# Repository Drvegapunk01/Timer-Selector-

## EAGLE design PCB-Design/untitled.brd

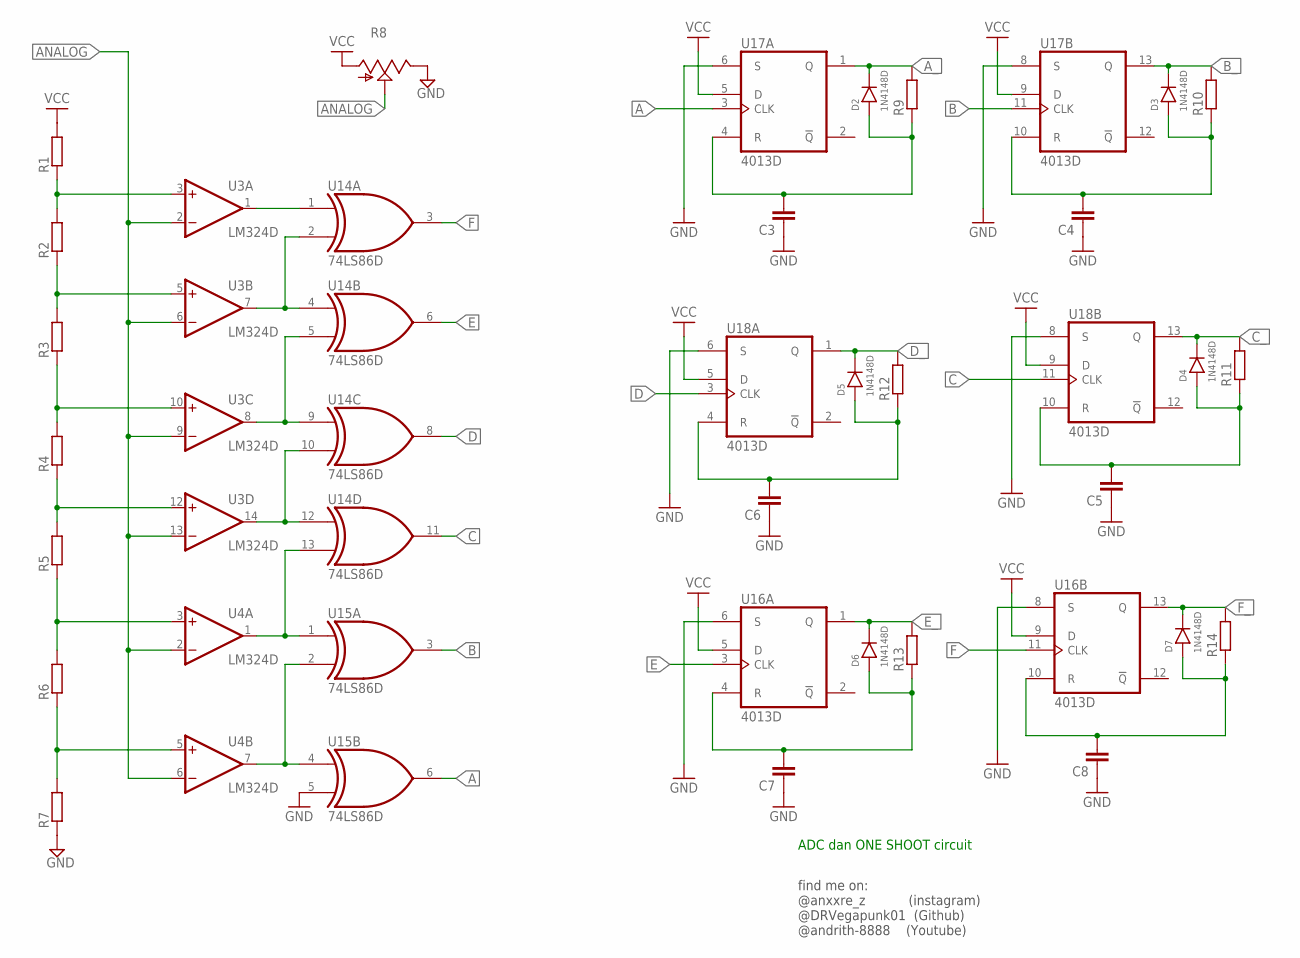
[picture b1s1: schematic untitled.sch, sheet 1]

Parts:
C3, C4, C5, C6, C7, C8: CAP-NON0805; SMD0805
D2, D3, D4, D5, D6, D7: 1N4148D; SOD80C
R1, R2, R3, R4, R5, R6, R7, R9, R10, R11, R12, R13, R14: RES0805; SMD0805
R8: TRIM_US-CT6; CT6
U3, U4: LM324D; SO14
U14, U15: 74LS86D; SO14
U16, U17, U18: 4013D; SO14

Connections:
A: U15.6 (O), U17.3 (CLK); also elsewhere on the board
ANALOG: R8.S, U3.2 (-IN), U3.6 (-IN), U3.9 (-IN), U3.13 (-IN), U4.2 (-IN), U4.6 (-IN); also elsewhere on the board
A_: D2.C (2), R9.2, U17.1 (Q); also elsewhere on the board
B: U15.3 (O), U17.11 (CLK); also elsewhere on the board
B_: D3.C (2), R10.2, U17.13 (Q); also elsewhere on the board
C: U14.11 (O), U18.11 (CLK); also elsewhere on the board
C_: D4.C (2), R11.2, U18.13 (Q); also elsewhere on the board
D: U14.8 (O), U18.3 (CLK); also elsewhere on the board
D_: D5.C (2), R12.2, U18.1 (Q); also elsewhere on the board
E: U14.6 (O), U16.3 (CLK); also elsewhere on the board
E_: D6.C (2), R13.2, U16.1 (Q); also elsewhere on the board
F: U14.3 (O), U16.11 (CLK); also elsewhere on the board
F_: D7.C (2), R14.2, U16.13 (Q); also elsewhere on the board
GND: C3.1, C4.1, C5.1, C6.1, C7.1, C8.1, R7.1, R8.E, U15.5 (I1), U16.6 (S), U16.8 (S), U17.6 (S), U17.8 (S), U18.6 (S), U18.8 (S); also elsewhere on the board
unnamed: R6.1, R7.2, U4.5 (+IN)
unnamed: R5.1, R6.2, U4.3 (+IN)
unnamed: R4.1, R5.2, U3.12 (+IN)
unnamed: R3.1, R4.2, U3.10 (+IN)
unnamed: R2.1, R3.2, U3.5 (+IN)
unnamed: R1.1, R2.2, U3.3 (+IN)
unnamed: U4.7 (OUT), U15.2 (I1), U15.4 (I0)
unnamed: U4.1 (OUT), U14.13 (I1), U15.1 (I0)
unnamed: U3.14 (OUT), U14.10 (I1), U14.12 (I0)
unnamed: C3.2, D2.A (1), R9.1, U17.4 (R)
unnamed: U3.8 (OUT), U14.5 (I1), U14.9 (I0)
unnamed: U3.7 (OUT), U14.2 (I1), U14.4 (I0)
unnamed: U3.1 (OUT), U14.1 (I0)
unnamed: C4.2, D3.A (1), R10.1, U17.10 (R)
unnamed: C5.2, D4.A (1), R11.1, U18.10 (R)
unnamed: C6.2, D5.A (1), R12.1, U18.4 (R)
unnamed: C7.2, D6.A (1), R13.1, U16.4 (R)
unnamed: C8.2, D7.A (1), R14.1, U16.10 (R)
VCC: R1.2, R8.A, U16.5 (D), U16.9 (D), U17.5 (D), U17.9 (D), U18.5 (D), U18.9 (D); also elsewhere on the board

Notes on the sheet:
ADC dan ONE SHOOT circuit
find me on: @anxxre_z (instagram) @DRVegapunk01 (Github) @andrith-8888 (Youtube)

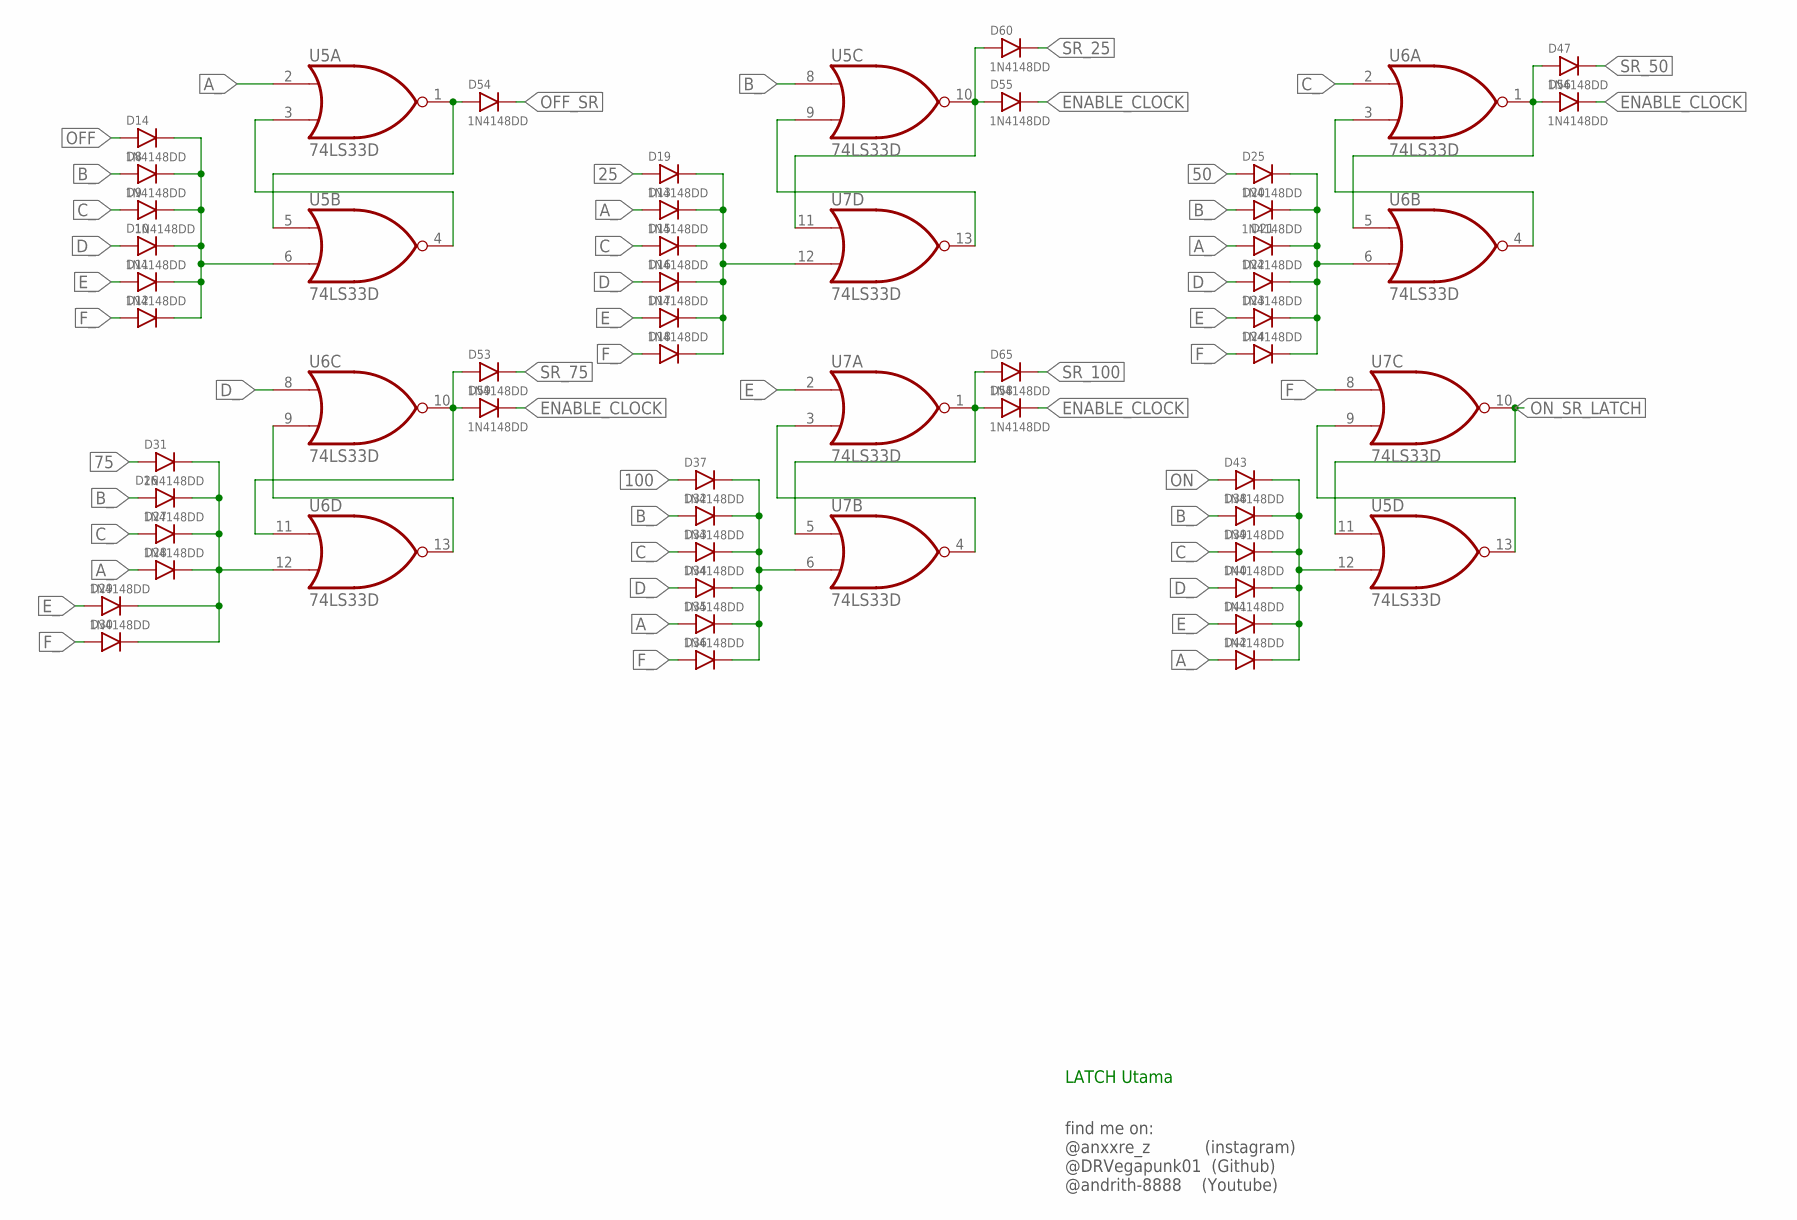
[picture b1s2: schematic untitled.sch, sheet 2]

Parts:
D8, D9, D10, D11, D12, D13, D14, D15, D16, D17, D18, D19, D20, D21, D22, D23, D24, D25, D26, D27, D28, D29, D30, D31, D32, D33, D34, D35, D36, D37, D38, D39, D40, D41, D42, D43, D47, D53, D54, D55, D56, D58, D59, D60, D65: 1N4148DD; SOD123
U5, U6, U7: 74LS33D; SO14

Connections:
25: D19.A (1); also elsewhere on the board
50: D25.A (1); also elsewhere on the board
75: D31.A (1); also elsewhere on the board
100: D37.A (1); also elsewhere on the board
A_: D13.A (1), D21.A (1), D28.A (1), D35.A (1), D42.A (1), U5.2 (I0); also elsewhere on the board
B_: D8.A (1), D20.A (1), D26.A (1), D32.A (1), D38.A (1), U5.8 (I0); also elsewhere on the board
C_: D9.A (1), D15.A (1), D27.A (1), D33.A (1), D39.A (1), U6.2 (I0); also elsewhere on the board
D_: D10.A (1), D16.A (1), D22.A (1), D34.A (1), D40.A (1), U6.8 (I0); also elsewhere on the board
ENABLE_CLOCK: D55.C (2), D56.C (2), D58.C (2), D59.C (2); also elsewhere on the board
E_: D11.A (1), D17.A (1), D23.A (1), D29.A (1), D41.A (1), U7.2 (I0); also elsewhere on the board
F_: D12.A (1), D18.A (1), D24.A (1), D30.A (1), D36.A (1), U7.8 (I0); also elsewhere on the board
unnamed: U5.3 (I1), U5.4 (O)
unnamed: D20.C (2), D21.C (2), D22.C (2), D23.C (2), D24.C (2), D25.C (2), U6.6 (I1)
unnamed: D8.C (2), D9.C (2), D10.C (2), D11.C (2), D12.C (2), D14.C (2), U5.6 (I1)
unnamed: D26.C (2), D27.C (2), D28.C (2), D29.C (2), D30.C (2), D31.C (2), U6.12 (I1)
unnamed: U6.9 (I1), U6.13 (O)
unnamed: D32.C (2), D33.C (2), D34.C (2), D35.C (2), D36.C (2), D37.C (2), U7.6 (I1)
unnamed: D38.C (2), D39.C (2), D40.C (2), D41.C (2), D42.C (2), D43.C (2), U5.12 (I1)
unnamed: U7.3 (I1), U7.4 (O)
unnamed: U5.9 (I1), U7.13 (O)
unnamed: U6.3 (I1), U6.4 (O)
unnamed: U5.13 (O), U7.9 (I1)
unnamed: D13.C (2), D15.C (2), D16.C (2), D17.C (2), D18.C (2), D19.C (2), U7.12 (I1)
OFF: D14.A (1)
OFF_SR: D54.C (2); also elsewhere on the board
ON: D43.A (1)
ON_SR_LATCH: U5.11 (I0), U7.10 (O); also elsewhere on the board
Q1: D54.A (1), U5.1 (O), U5.5 (I0)
Q2: D55.A (1), D60.A (1), U5.10 (O), U7.11 (I0)
Q3: D47.A (1), D56.A (1), U6.1 (O), U6.5 (I0)
Q4: D53.A (1), D59.A (1), U6.10 (O), U6.11 (I0)
Q5: D58.A (1), D65.A (1), U7.1 (O), U7.5 (I0)
SR_25: D60.C (2); also elsewhere on the board
SR_50: D47.C (2); also elsewhere on the board
SR_75: D53.C (2); also elsewhere on the board
SR_100: D65.C (2)

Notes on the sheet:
LATCH Utama
find me on: @anxxre_z (instagram) @DRVegapunk01 (Github) @andrith-8888 (Youtube)

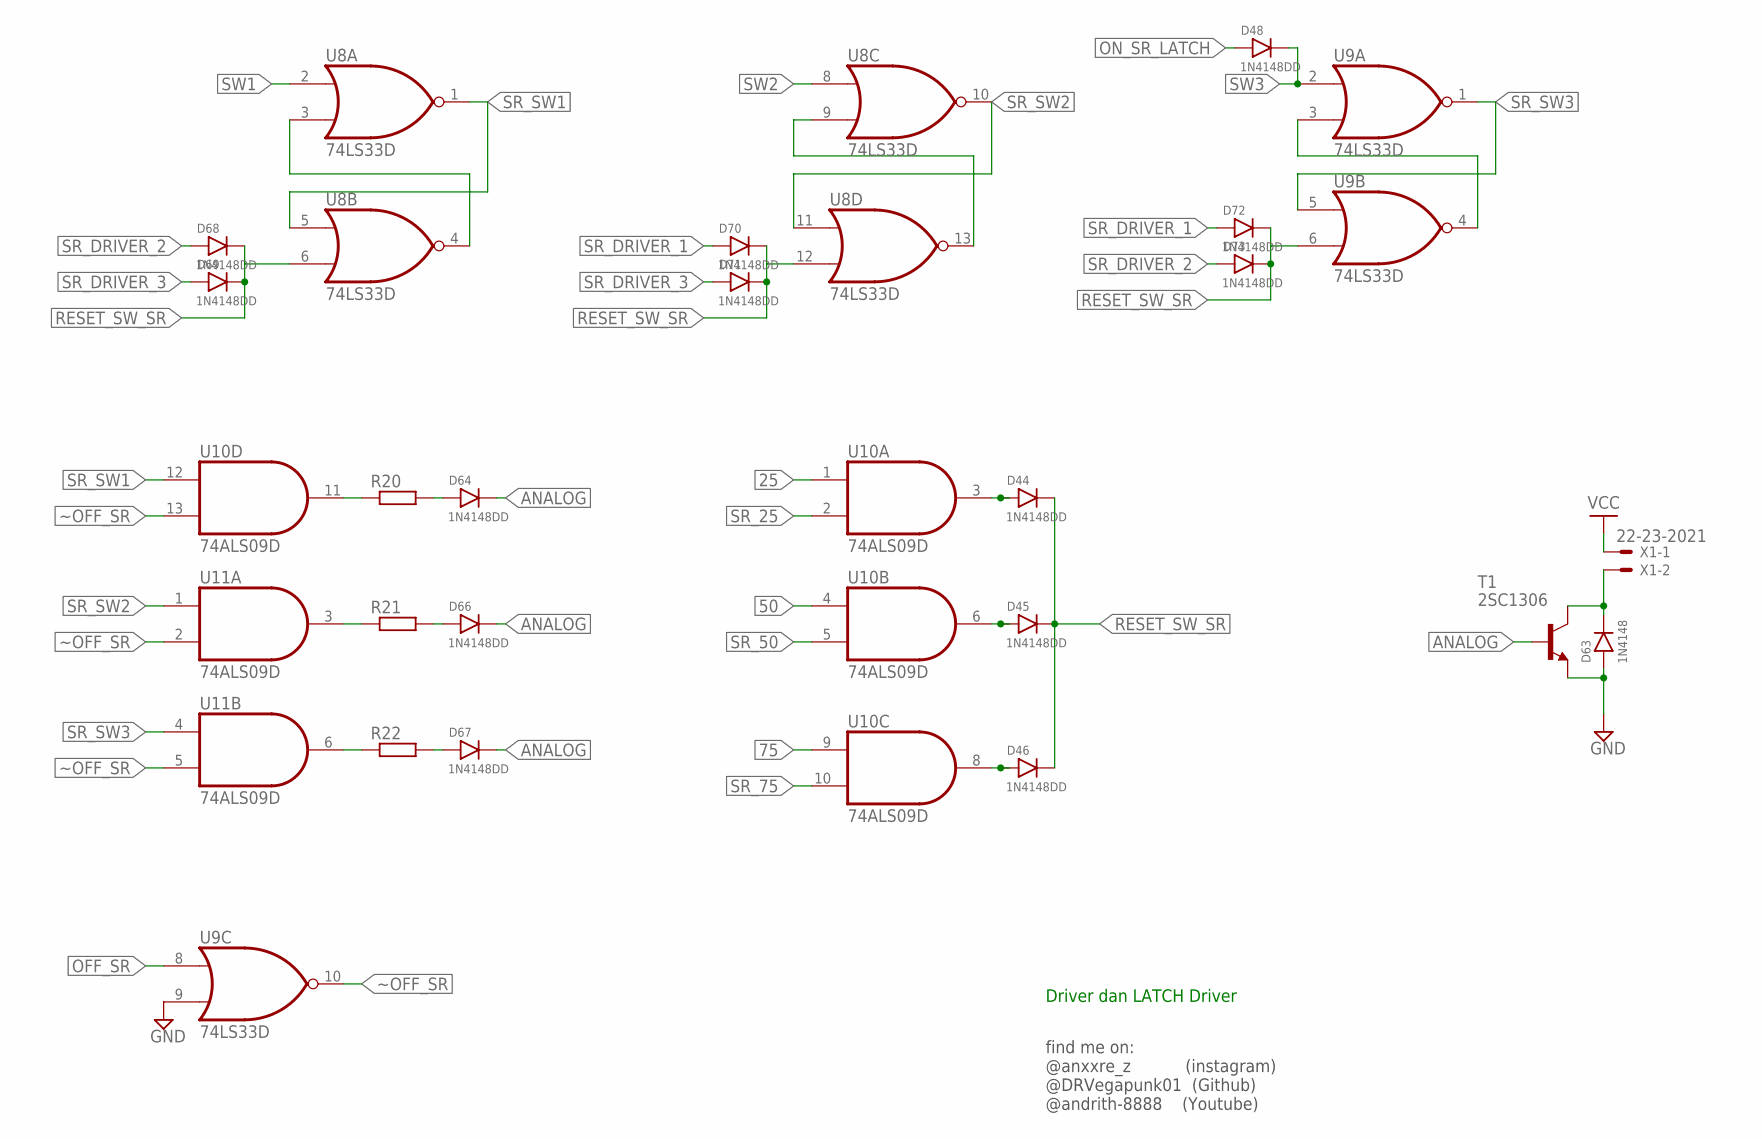
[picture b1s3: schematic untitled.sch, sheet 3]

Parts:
D44, D45, D46, D48, D64, D66, D67, D68, D69, D70, D71, D72, D73: 1N4148DD; SOD123
D63: 1N4148; DIODE
R20, R21, R22: RES0805; SMD0805
T1: 2SC1306; TO220BV
U8, U9: 74LS33D; SO14
U10, U11: 74ALS09D; SO14
X1: 22-23-2021

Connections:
25: U10.1 (I0); also elsewhere on the board
50: U10.4 (I0); also elsewhere on the board
75: U10.9 (I0); also elsewhere on the board
ANALOG: D64.C (2), D66.C (2), D67.C (2), T1.1 (B); also elsewhere on the board
GND: D63.1, T1.3 (E), U9.9 (I1); also elsewhere on the board
unnamed: R22.1, U11.6 (O)
unnamed: D67.A (1), R22.2
unnamed: U8.3 (I1), U8.4 (O)
unnamed: D66.A (1), R21.2
unnamed: R21.1, U11.3 (O)
unnamed: D63.2, T1.2 (C), X1.2
unnamed: D64.A (1), R20.2
unnamed: R20.1, U10.11 (O)
unnamed: U8.9 (I1), U8.13 (O)
unnamed: D44.A (1), U10.3 (O)
unnamed: D45.A (1), U10.6 (O)
unnamed: D46.A (1), U10.8 (O)
unnamed: U9.3 (I1), U9.4 (O)
OFF_SR: U9.8 (I0); also elsewhere on the board
ON_SR_LATCH: D48.A (1); also elsewhere on the board
RESET_SW_SR: D44.C (2), D45.C (2), D46.C (2), D68.C (2), D69.C (2), D70.C (2), D71.C (2), D72.C (2), D73.C (2), U8.6 (I1), U8.12 (I1), U9.6 (I1); also elsewhere on the board
SR_25: U10.2 (I1); also elsewhere on the board
SR_50: U10.5 (I1); also elsewhere on the board
SR_75: U10.10 (I1); also elsewhere on the board
SR_DRIVER_1: D70.A (1), D72.A (1)
SR_DRIVER_2: D68.A (1), D73.A (1)
SR_DRIVER_3: D69.A (1), D71.A (1)
SR_SW1: U8.1 (O), U8.5 (I0), U10.12 (I0)
SR_SW2: U8.10 (O), U8.11 (I0), U11.1 (I0)
SR_SW3: U9.1 (O), U9.5 (I0), U11.4 (I0)
SW1: U8.2 (I0); also elsewhere on the board
SW2: U8.8 (I0); also elsewhere on the board
SW3: D48.C (2), U9.2 (I0); also elsewhere on the board
VCC: X1.1; also elsewhere on the board
~OFF_SR: U9.10 (O), U10.13 (I1), U11.2 (I1), U11.5 (I1)

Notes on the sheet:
Driver dan LATCH Driver
find me on: @anxxre_z (instagram) @DRVegapunk01 (Github) @andrith-8888 (Youtube)

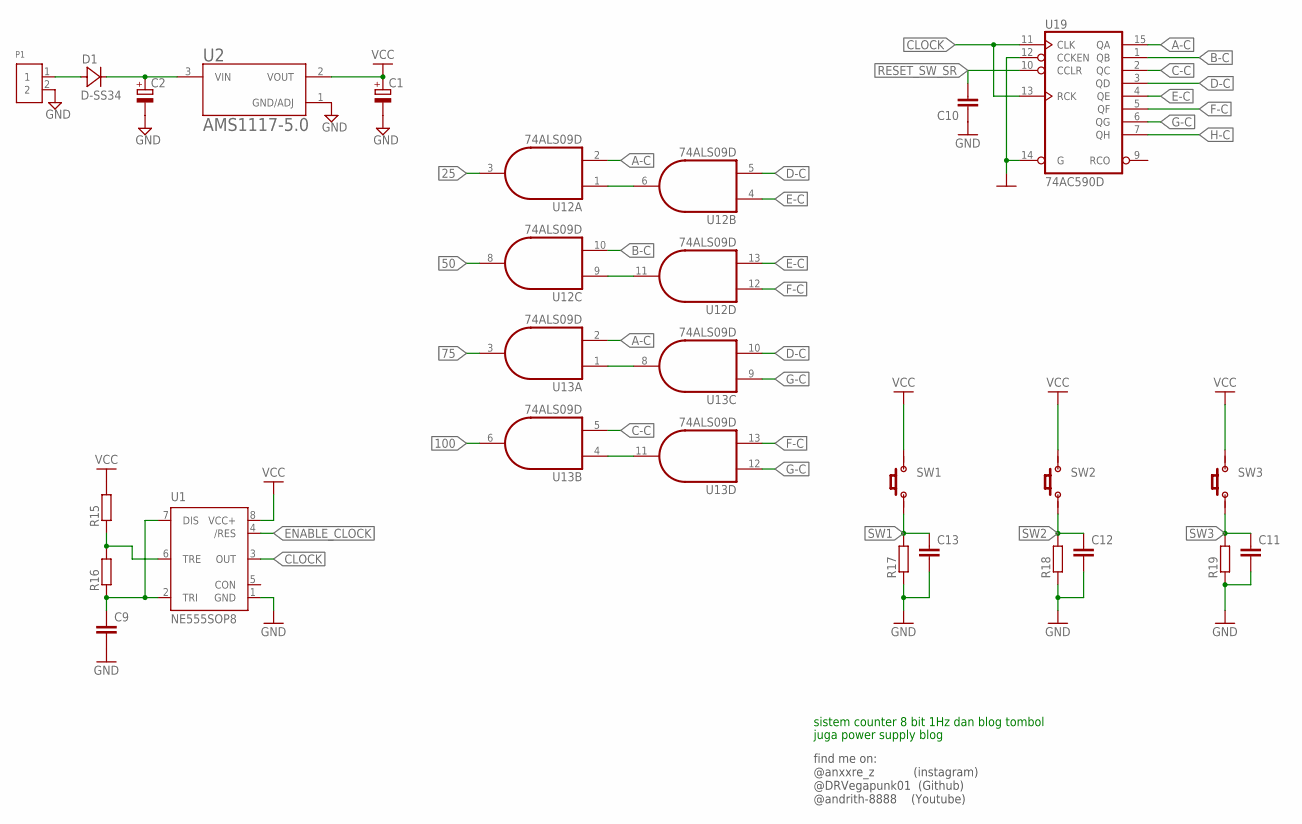
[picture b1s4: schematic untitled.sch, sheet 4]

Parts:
C1, C2: CAP-POLARE5-4; E5-4
C9, C10, C11, C12, C13: CAP-NON0805; SMD0805
D1: D-SS34; SMA
P1: TERMINALBLOK; TB-2P
R15, R16, R17, R18, R19: RES0805; SMD0805
SW1, SW2, SW3: PUSH_BUTTON4P; PUSH_BUTTON_4P
U1: NE555SOP8; SO08
U2: AMS1117-5.0; SOT229P700X180-4N
U12, U13: 74ALS09D; SO14
U19: 74AC590D; SO16

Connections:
25: U12.3 (O); also elsewhere on the board
50: U12.8 (O); also elsewhere on the board
75: U13.3 (O); also elsewhere on the board
100: U13.6 (O); also elsewhere on the board
A-C: U12.2 (I1), U13.2 (I1), U19.15 (QA)
B-C: U12.10 (I1), U19.1 (QB)
C-C: U13.5 (I1), U19.2 (QC)
CLOCK: U1.3 (OUT), U19.11 (CLK), U19.13 (RCK)
D-C: U12.5 (I1), U13.10 (I1), U19.3 (QD)
E-C: U12.4 (I0), U12.13 (I1), U19.4 (QE)
ENABLE_CLOCK: U1.4 (/RES); also elsewhere on the board
F-C: U12.12 (I0), U13.13 (I1), U19.5 (QF)
G-C: U13.9 (I0), U13.12 (I0), U19.6 (QG)
GND: C1.-, C2.-, C9.2, C10.2, C11.2, C12.2, C13.2, P1.2, R17.1, R18.1, R19.1, U1.1 (GND), U2.1 (GND/ADJ), U19.12 (CCKEN), U19.14 (G); also elsewhere on the board
H-C: U19.7 (QH)
unnamed: D1.A, P1.1
unnamed: C2.+, D1.C, U2.3 (VIN)
unnamed: C9.1, R16.1, U1.2 (TRI), U1.7 (DIS)
unnamed: R15.1, R16.2, U1.6 (TRE)
unnamed: U12.1 (I0), U12.6 (O)
unnamed: U12.9 (I0), U12.11 (O)
unnamed: U13.1 (I0), U13.8 (O)
unnamed: U13.4 (I0), U13.11 (O)
RESET_SW_SR: C10.1, U19.10 (CCLR); also elsewhere on the board
SW1: C13.1, R17.2, SW1.1, SW1.2 (1); also elsewhere on the board
SW2: C12.1, R18.2, SW2.1, SW2.2 (1); also elsewhere on the board
SW3: C11.1, R19.2, SW3.1, SW3.2 (1); also elsewhere on the board
VCC: C1.+, R15.2, SW1.3 (2), SW1.4 (2), SW2.3 (2), SW2.4 (2), SW3.3 (2), SW3.4 (2), U1.8 (VCC+), U2.2 (VOUT); also elsewhere on the board

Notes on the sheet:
sistem counter 8 bit 1Hz dan blog tombol
juga power supply blog
find me on: @anxxre_z (instagram) @DRVegapunk01 (Github) @andrith-8888 (Youtube)

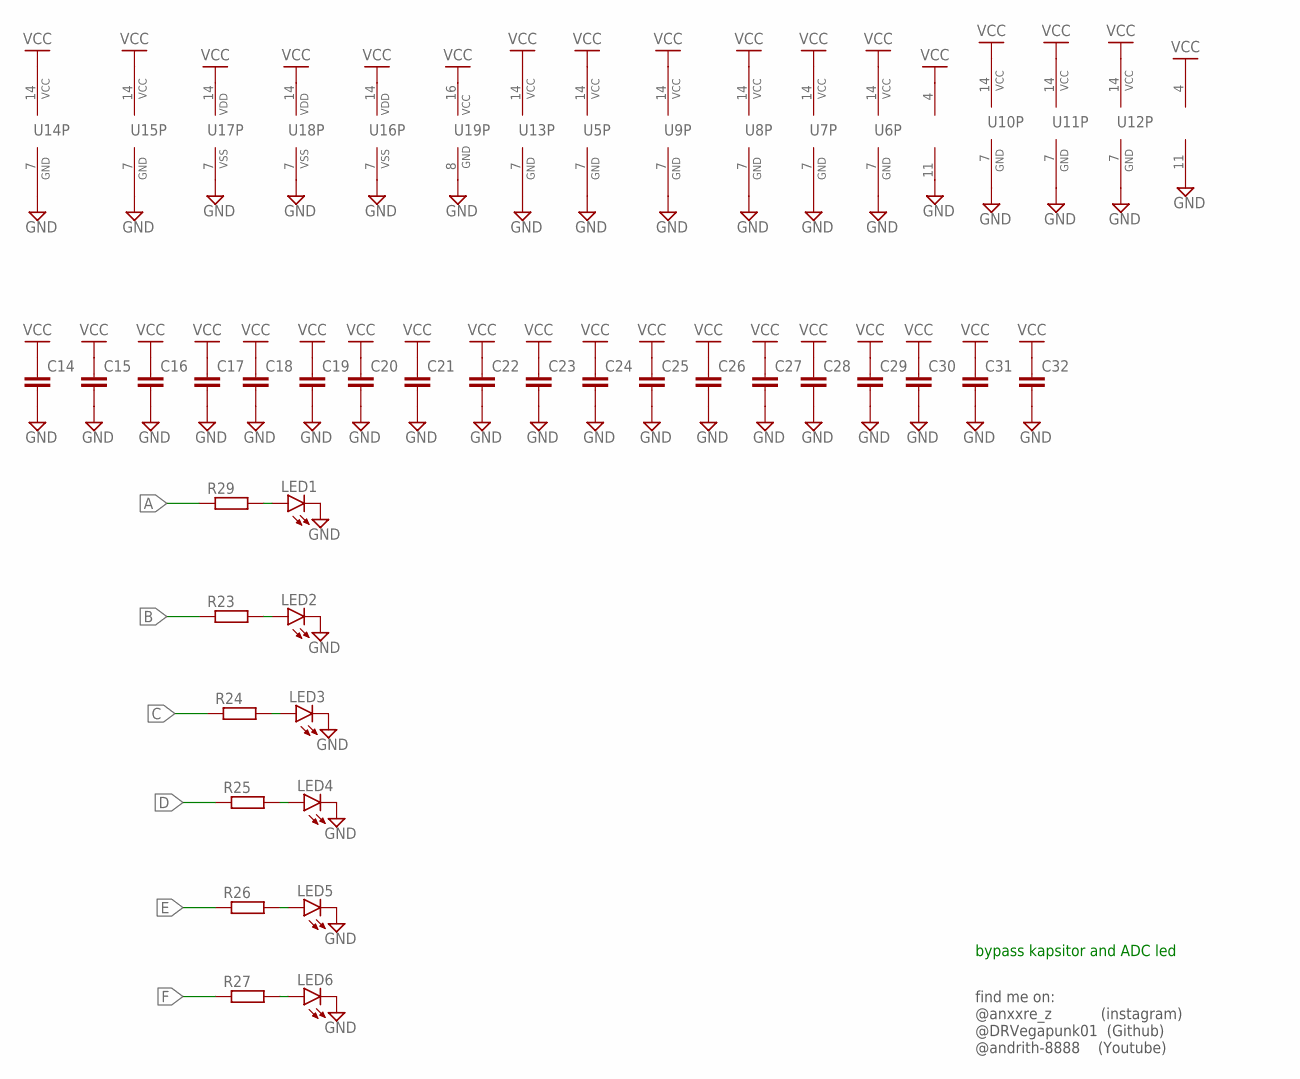
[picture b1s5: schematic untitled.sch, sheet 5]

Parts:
C14, C15, C16, C17, C18, C19, C20, C21, C22, C23, C24, C25, C26, C27, C28, C29, C30, C31, C32: CAP-NON0805; SMD0805
LED1, LED2, LED3, LED4, LED5, LED6: LED0805; CHIPLED_0805
R23, R24, R25, R26, R27, R29: RES0805; SMD0805
U3, U4: LM324D; SO14
U5, U6, U7, U8, U9: 74LS33D; SO14
U10, U11, U12, U13: 74ALS09D; SO14
U14, U15: 74LS86D; SO14
U16, U17, U18: 4013D; SO14
U19: 74AC590D; SO16

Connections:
A: R29.1; also elsewhere on the board
B: R23.1; also elsewhere on the board
C: R24.1; also elsewhere on the board
D: R25.1; also elsewhere on the board
E: R26.1; also elsewhere on the board
F: R27.1; also elsewhere on the board
GND: C14.2, C15.2, C16.2, C17.2, C18.2, C19.2, C20.2, C21.2, C22.2, C23.2, C24.2, C25.2, C26.2, C27.2, C28.2, C29.2, C30.2, C31.2, C32.2, LED1.C, LED2.C, LED3.C, LED4.C, LED5.C, LED6.C, U3.11 (V-), U4.11 (V-), U5.7 (GND), U6.7 (GND), U7.7 (GND), U8.7 (GND), U9.7 (GND), U10.7 (GND), U11.7 (GND), U12.7 (GND), U13.7 (GND), U14.7 (GND), U15.7 (GND), U16.7 (VSS), U17.7 (VSS), U18.7 (VSS), U19.8 (GND); also elsewhere on the board
unnamed: LED3.A, R24.2
unnamed: LED4.A, R25.2
unnamed: LED5.A, R26.2
unnamed: LED6.A, R27.2
unnamed: LED1.A, R29.2
unnamed: LED2.A, R23.2
VCC: C14.1, C15.1, C16.1, C17.1, C18.1, C19.1, C20.1, C21.1, C22.1, C23.1, C24.1, C25.1, C26.1, C27.1, C28.1, C29.1, C30.1, C31.1, C32.1, U3.4 (V+), U4.4 (V+), U5.14 (VCC), U6.14 (VCC), U7.14 (VCC), U8.14 (VCC), U9.14 (VCC), U10.14 (VCC), U11.14 (VCC), U12.14 (VCC), U13.14 (VCC), U14.14 (VCC), U15.14 (VCC), U16.14 (VDD), U17.14 (VDD), U18.14 (VDD), U19.16 (VCC); also elsewhere on the board

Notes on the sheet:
find me on: @anxxre_z (instagram) @DRVegapunk01 (Github) @andrith-8888 (Youtube)
bypass kapsitor and ADC led

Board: 2 copper layers, 157 parts (29 on the bottom side), 106 nets, no tracks yet.
